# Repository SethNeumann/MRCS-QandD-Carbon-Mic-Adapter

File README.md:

# MRCS-QandD-Carbon-Mic-Adapter

## License: Creative Commons Attribution-NonCommercial-ShareAlike

I designed this adapter after working with Lee Nicholas on the phone system for the Utah, Colorado and Western. Lee has a carbon mic in a metal enclosure on a boom
over his CTC machine for the Dispatcher's use.  Lee had also been using my Active Telephone Speech Network (ATSN) for use with a computer headset, powered speaker and a 
footswitch. At one time he wanted to use the ATSN with the carbon mic, but ATSN supports dynamics and Electrets, but ATSN doesn't supply enough current for a carbon mic.
This adapter takes filtered 12V (or any voltage up to 24V with changes to the dropping resistor) and powers a carbon mic. The mic is in paralled with 600:600 isolation
transformer (in series with a 1uF blocking cap) and provides line level audio out.  This audio can feed an ATSN or any line to power amplifier, numerous powered speakers 
and and small amplifier boards are avaialable which will work well with the MRCS-QandD-Carbon-Mic-Adapter.

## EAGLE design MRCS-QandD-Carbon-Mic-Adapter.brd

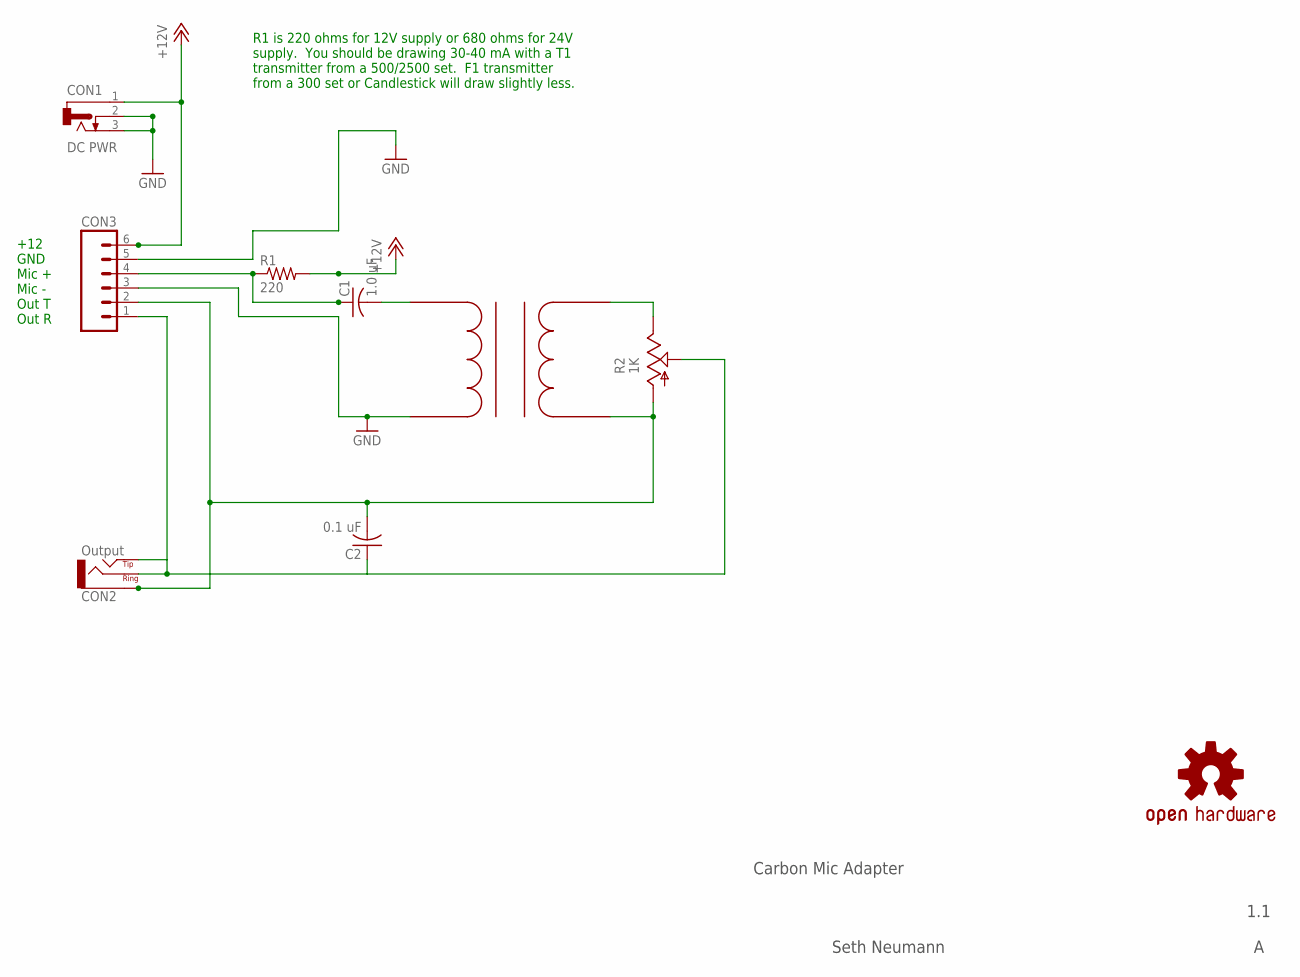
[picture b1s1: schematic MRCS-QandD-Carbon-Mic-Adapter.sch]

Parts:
C1: 1.0 uF; C-PTH-0.100
C2: 0.1 uF; C-PTH-0.100
CON1: DC PWR; DCJ0202
CON2: Output; AUDIO-JACK-3.5MM_STEREO
CON3: CONNECTOR-M063.5MM-6; SCREWTERMINAL-3.5MM-6
OSHW1: DOC-OSHW-LOGO-M; OSHW-LOGO-M
R1: 220; AXIAL-0.4-RES
R2: 1K; RS3
U$1: EI14_600-600; XFMR580X500

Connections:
+12V: CON1.1, CON3.6, R1.P$2 (2)
GND: CON1.2, CON1.3, CON3.3, CON3.5, U$1.PBOTTOM
MIC+: C1.1, CON3.4, R1.P$1 (1)
unnamed: R2.E, U$1.STOP
unnamed: C1.2, U$1.PTOP
unnamed: C2.1, CON2.RING, CON2.TIP, CON3.1, R2.S
OUTT: C2.2, CON2.GND (SLEEVE), CON3.2, R2.A, U$1.SBOTTOM

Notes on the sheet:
Carbon Mic Adapter
1.1
Seth Neumann
+12 GND Mic + Mic - Out T Out R
R1 is 220 ohms for 12V supply or 680 ohms for 24V supply. You should be drawing 30-40 mA with a T1 transmitter from a 500/2500 set. F1 transmitter from a 300 set or Candlestick will draw slightly less.

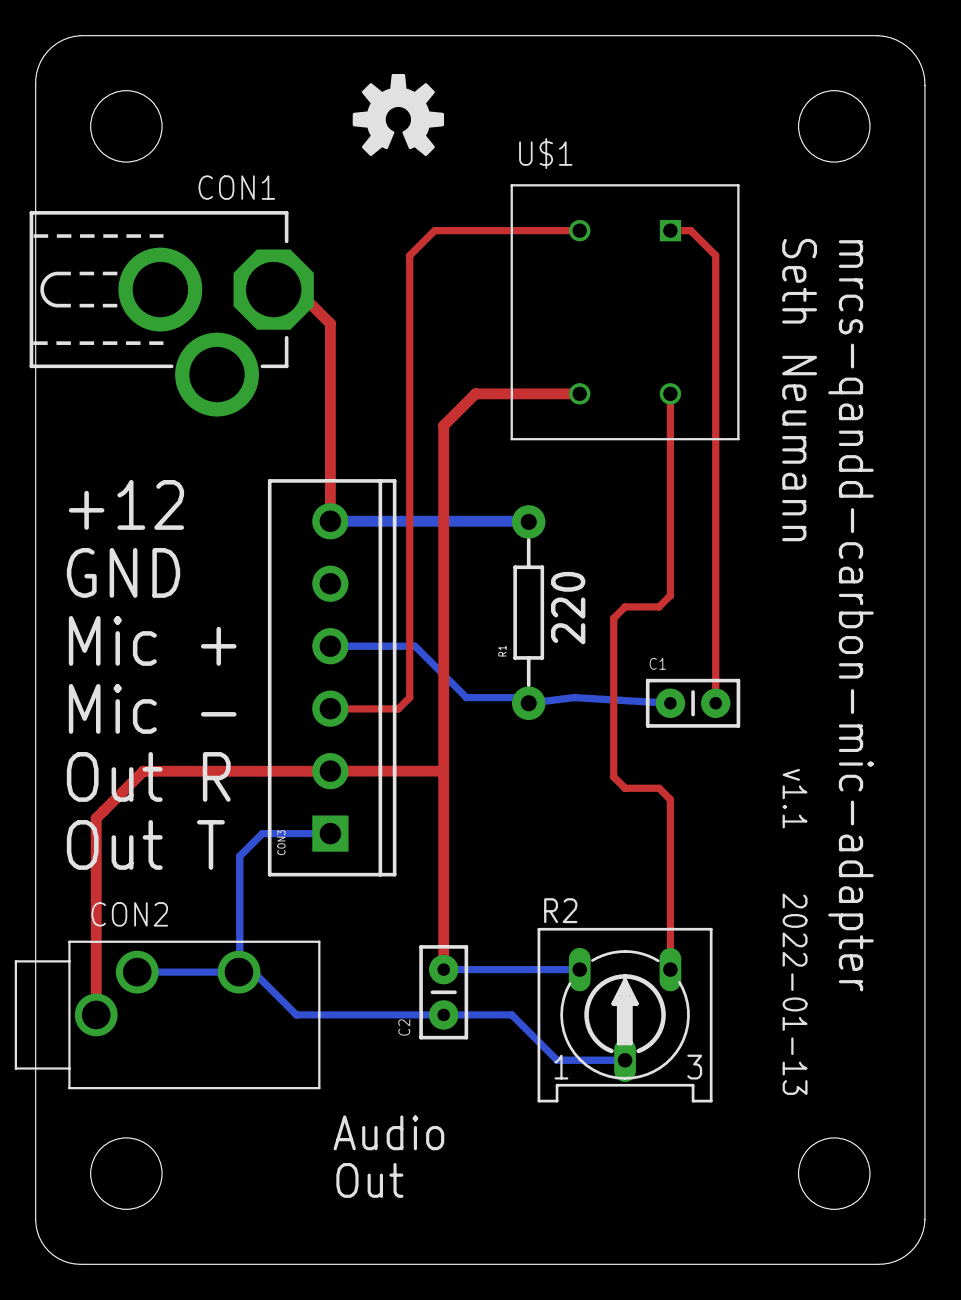
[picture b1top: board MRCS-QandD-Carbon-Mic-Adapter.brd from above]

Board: 2 copper layers, 49.8 x 68.8 mm, 12 parts (0 on the bottom side), 7 nets.

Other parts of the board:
U$2: BOARD-DINRAIL-2.7IN-5CM
U$3: MRCSLOGOTOP
U$4: CA-PROP65WARNING

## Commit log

2022-01-02 changed names of templates
    changed names of templates
2022-01-03 Initial design sent to PCB Fab on 1/2/22
    First pass board, easier to make the PCB than fool with a bread board.
2022-02-02 Version 1.1 fixed input ground, general cleanup
    Version 1.1 fixed input ground, general cleanup
2022-02-08 repository clean up
    removed various work files from the repository
2022-02-08 after 2nd revision
    fixed floating ground, cleaned up labels
2023-09-16 pdfs of Schematic and layout
    cleaning up documentation

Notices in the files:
parts and their libraries:
SPCoast: http://freedomdefined.org/OSHW Creative Commons - Attribution - ShareAlike 3.0
